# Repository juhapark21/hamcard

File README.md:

# Ham radio card 
A small dashboard that displays propagation conditions with colored LEDs. 

## How to use 
Replace the placeholder values in the firmware with the SSID and password of your known wifi network. This makes it so that the microcontroller can connect to a network and access the weather data online.  

Assemble the PCB. Components are sized to be possible to hand-solder - A few components are through-hole for ease of hand-soldering.  

After assembling the PCB, flash the firmware onto the XIAO ESP32C3 ([instructions here](https://wiki.seeedstudio.com/xiao_esp32c3_with_micropython/)). 

Connect the ESP32 to a power source via USB-C and turn the power switch ON. The indicator light on the bottom right corner will turn on. 

As long as the board is connected to a network and a power source, it will update its data every hour and the indicator lights will change accordingly. 

LED indicator lights ordered by general severity: 
- Green: Good-Great
- Yellow: Fair
- Orange: Fair-Poor
- Red: Poor 

To turn off, turn the power switch OFF then disconnect the board from the power source. 

## Why 
Propagation info like this is like the weather report for radio nerds. It helps determine which bands you should work, or approximately how far your signal will reach. 

I initially made it because I wanted a fun useful business card. That idea got a bit out of hand (the thickness and power consumption of this does not make it very suitable to be used as a card), but I ended up with a nice physical dashboard showing useful weather information for amateur radio. 

Most existing dashboards are online, so I wanted this to be a physical object separate from tabs or apps on my computer. 

## Process 
The design and build process is documented in detail [here](https://fallout.hackclub.com/projects/3668). Even though this project was smaller-scale, it involved a lot of trial-and-error. 

## Credits  
Thank you Paul N0NBH for the solar-terrestrial [data](https://www.hamqsl.com/).  

## Zine page

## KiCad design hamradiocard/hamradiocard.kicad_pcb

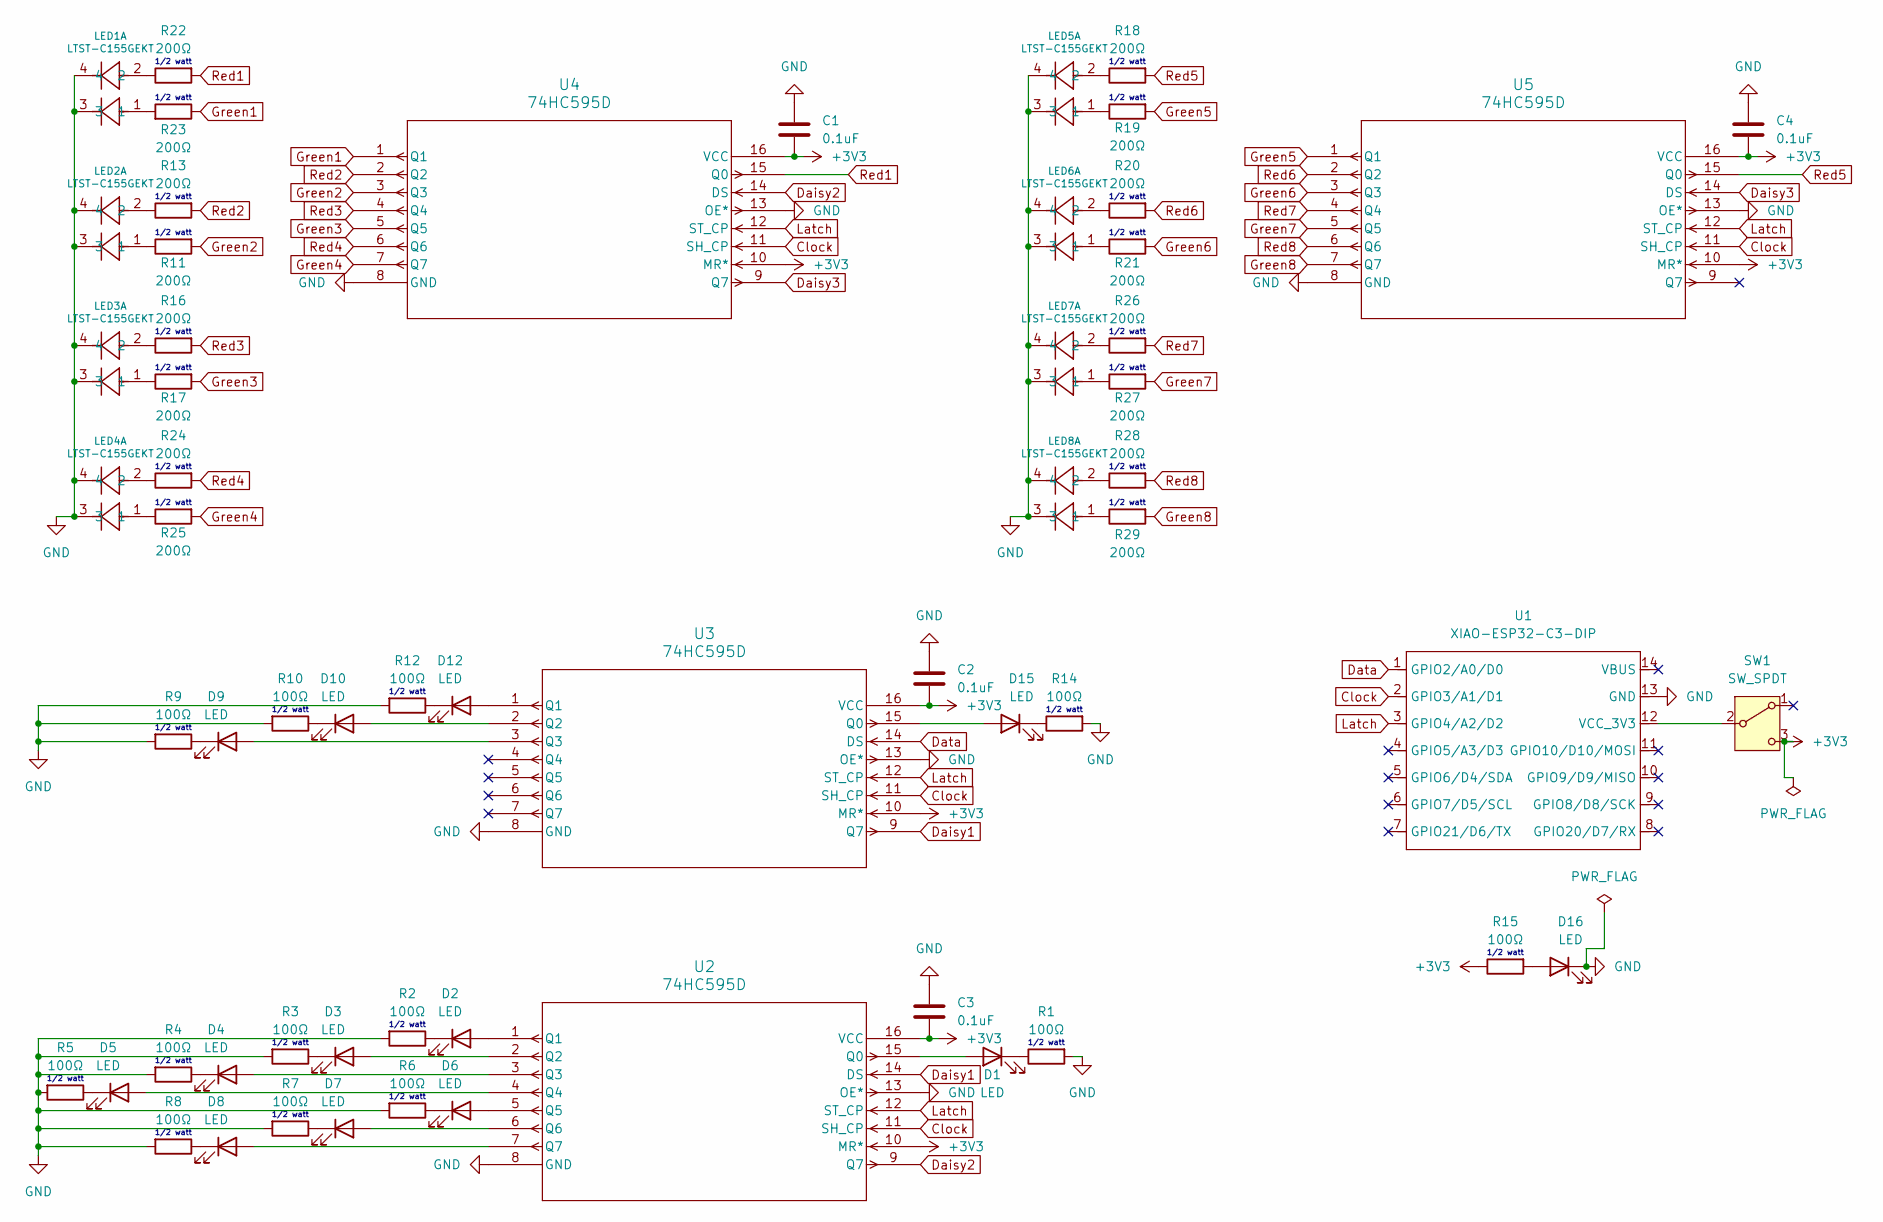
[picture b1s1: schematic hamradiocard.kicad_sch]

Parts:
C1, C2, C3, C4: 0.1uF; C_1206_3216Metric_Pad1.33x1.80mm_HandSolder
D1, D2, D3, D4, D5, D6, D7, D8, D9, D10, D12, D15, D16: LED; LED_1206_3216Metric_Pad1.42x1.75mm_HandSolder
LED1, LED2, LED3, LED4, LED5, LED6, LED7, LED8: LTST-C155GEKT; DIODE_LTST-C155GEKT_LTO-M
R1, R2, R3, R4, R5, R6, R7, R8, R9, R10, R12, R14, R15: 100Ω; R_1206_3216Metric_Pad1.30x1.75mm_HandSolder
R11, R13, R16, R17, R18, R19, R20, R21, R22, R23, R24, R25, R26, R27, R28, R29: 200Ω; R_1206_3216Metric_Pad1.30x1.75mm_HandSolder
SW1: SW_SPDT; SW3_SLW-883935-2A-D_SSY
U1: XIAO-ESP32-C3-DIP; XIAO-ESP32C3-DIP
U2, U3, U4, U5: 74HC595D; SOT109-1_NXP

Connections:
+3V3: C1.2, C2.2, C3.2, C4.2, R15.1, SW1.3 (C), U2.10 (MR*), U2.16 (VCC), U3.10 (MR*), U3.16 (VCC), U4.10 (MR*), U4.16 (VCC), U5.10 (MR*), U5.16 (VCC)
Clock: U1.2 (GPIO3/A1/D1), U2.11 (SH_CP), U3.11 (SH_CP), U4.11 (SH_CP), U5.11 (SH_CP)
Daisy1: U2.14 (DS), U3.9 (Q7)
Daisy2: U2.9 (Q7), U4.14 (DS)
Daisy3: U4.9 (Q7), U5.14 (DS)
Data: U1.1 (GPIO2/A0/D0), U3.14 (DS)
GND: C1.1, C2.1, C3.1, C4.1, D16.1 (K), LED1.3, LED1.4, LED2.3, LED2.4, LED3.3, LED3.4, LED4.3, LED4.4, LED5.3, LED5.4, LED6.3, LED6.4, LED7.3, LED7.4, LED8.3, LED8.4, R1.2, R2.2, R3.2, R4.2, R5.2, R6.2, R7.2, R8.2, R9.2, R10.2, R12.2, R14.2, U1.13 (GND), U2.8 (GND), U2.13 (OE*), U3.8 (GND), U3.13 (OE*), U4.8 (GND), U4.13 (OE*), U5.8 (GND), U5.13 (OE*)
Green1: R23.1, U4.1 (Q1)
Green2: R11.2, U4.3 (Q3)
Green3: R17.2, U4.5 (Q5)
Green4: R25.2, U4.7 (Q7)
Green5: R19.2, U5.1 (Q1)
Green6: R21.2, U5.3 (Q3)
Green7: R27.2, U5.5 (Q5)
Green8: R29.2, U5.7 (Q7)
Latch: U1.3 (GPIO4/A2/D2), U2.12 (ST_CP), U3.12 (ST_CP), U4.12 (ST_CP), U5.12 (ST_CP)
unnamed: D1.2 (A), U2.15 (Q0)
unnamed: D1.1 (K), R1.1
unnamed: D2.2 (A), U2.1 (Q1)
unnamed: D2.1 (K), R2.1
unnamed: D3.2 (A), U2.2 (Q2)
unnamed: D3.1 (K), R3.1
unnamed: D4.2 (A), U2.3 (Q3)
unnamed: D4.1 (K), R4.1
unnamed: D5.2 (A), U2.4 (Q4)
unnamed: D5.1 (K), R5.1
unnamed: D6.2 (A), U2.5 (Q5)
unnamed: D6.1 (K), R6.1
unnamed: D7.2 (A), U2.6 (Q6)
unnamed: D7.1 (K), R7.1
unnamed: D8.2 (A), U2.7 (Q7)
unnamed: D8.1 (K), R8.1
unnamed: D9.2 (A), U3.3 (Q3)
unnamed: D9.1 (K), R9.1
unnamed: D10.2 (A), U3.2 (Q2)
unnamed: D10.1 (K), R10.1
unnamed: D12.2 (A), U3.1 (Q1)
unnamed: D12.1 (K), R12.1
unnamed: D15.2 (A), U3.15 (Q0)
unnamed: D15.1 (K), R14.1
unnamed: D16.2 (A), R15.2
unnamed: LED1.1, R23.2
unnamed: LED1.2, R22.1
unnamed: LED2.1, R11.1
unnamed: LED2.2, R13.1
unnamed: LED3.1, R17.1
unnamed: LED3.2, R16.1
unnamed: LED4.1, R25.1
unnamed: LED4.2, R24.1
unnamed: LED5.1, R19.1
unnamed: LED5.2, R18.1
unnamed: LED6.1, R21.1
unnamed: LED6.2, R20.1
unnamed: LED7.1, R27.1
unnamed: LED7.2, R26.1
unnamed: LED8.1, R29.1
unnamed: LED8.2, R28.1
unnamed: SW1.2 (B), U1.12 (VCC_3V3)
Red1: R22.2, U4.15 (Q0)
Red2: R13.2, U4.2 (Q2)
Red3: R16.2, U4.4 (Q4)
Red4: R24.2, U4.6 (Q6)
Red5: R18.2, U5.15 (Q0)
Red6: R20.2, U5.2 (Q2)
Red7: R26.2, U5.4 (Q4)
Red8: R28.2, U5.6 (Q6)

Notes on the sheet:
1/2 watt

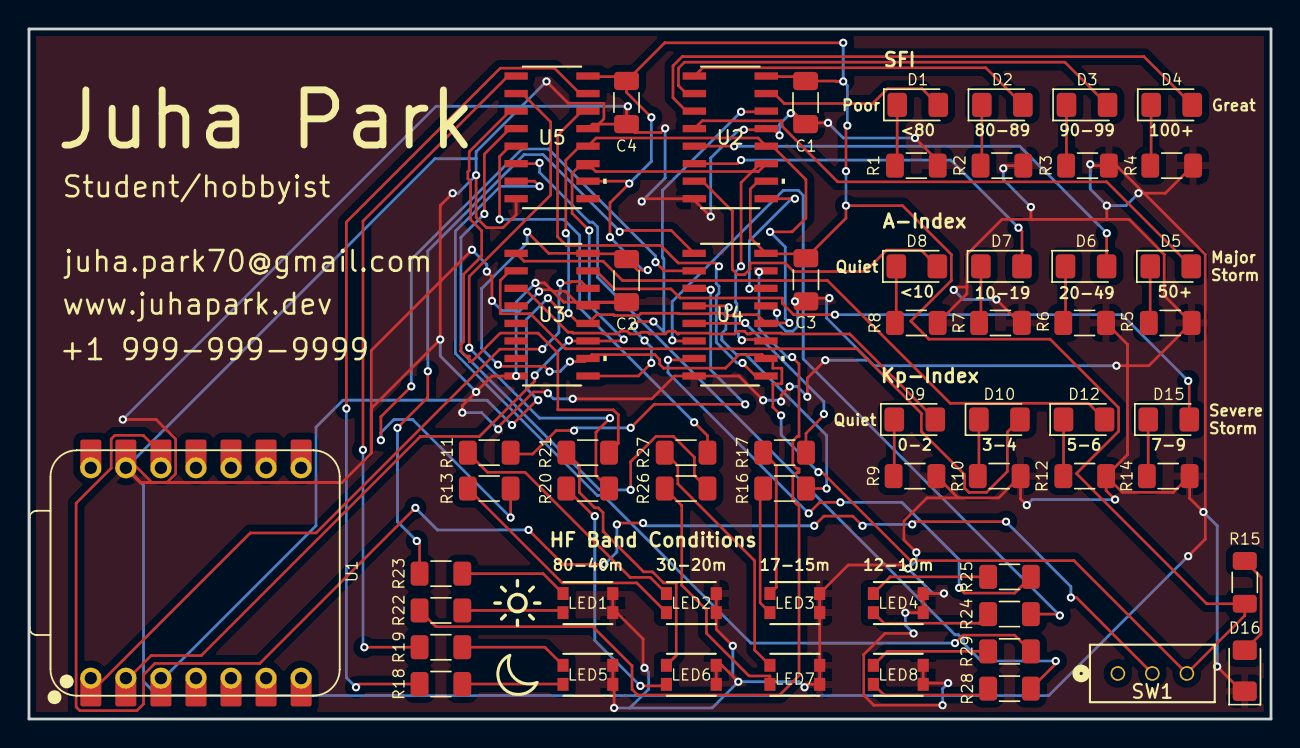
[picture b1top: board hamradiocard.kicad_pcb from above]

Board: 2 copper layers, 90.0 x 50.0 mm, 60 parts (0 on the bottom side), 66 nets.

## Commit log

2026-06-12 Add zine
2026-06-12 Organize repository
2026-06-14 Update bom
2026-06-14 Update zine
2026-06-17 Update QR code
